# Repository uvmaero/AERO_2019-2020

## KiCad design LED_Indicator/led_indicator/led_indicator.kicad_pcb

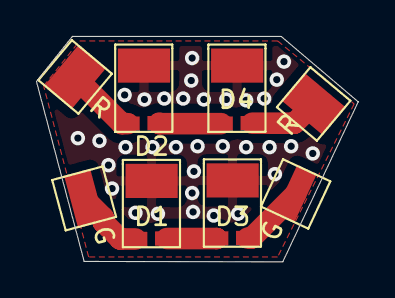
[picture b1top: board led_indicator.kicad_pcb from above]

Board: 2 copper layers, 17.9 x 12.5 mm, 8 parts (0 on the bottom side), 7 nets.

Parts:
D1, D2, D3, D4: LED_PAD; LXML-PM01
G: TestPoint; TestPoint_Pad_2.5x2.5mm
G#2: TestPoint; TestPoint_Pad_2.5x2.5mm
R: TestPoint; TestPoint_Pad_2.5x2.5mm
R#2: TestPoint; TestPoint_Pad_2.5x2.5mm

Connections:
/G_IN: D2.2, G#2.1
/G_OUT: D4.1, G.1
/R_IN: D1.2, R#2.1
/R_OUT: D3.1, R.1
/THM: D1.3, D2.3, D3.3, D4.3
unnamed: D1.1, D3.2
unnamed: D2.1, D4.2

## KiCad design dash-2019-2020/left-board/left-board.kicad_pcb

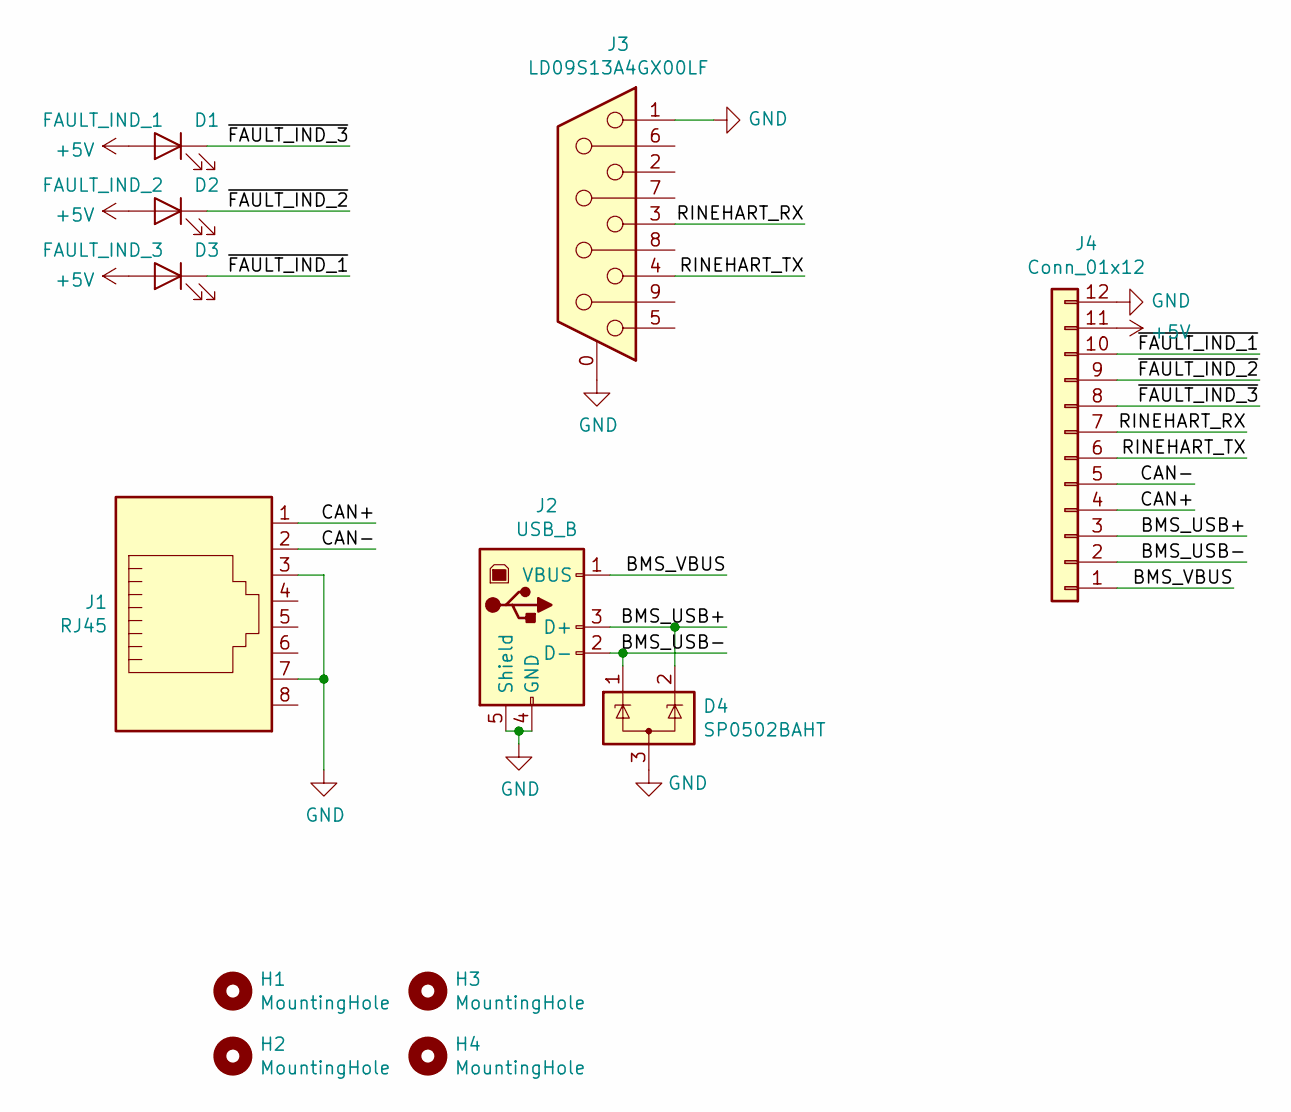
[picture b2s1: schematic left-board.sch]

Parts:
D1: FAULT_IND_1; LED_D5.0mm
D2: FAULT_IND_2; LED_D5.0mm
D3: FAULT_IND_3; LED_D5.0mm
D4: SP0502BAHT; SOT-23
H1, H2, H3, H4: MountingHole; MountingHole_3.2mm_M3
J1: RJ45; RJ45_Amphenol_54602-x08_Horizontal
J2: USB_B; USB_B_OST_USB-B1HSxx_Horizontal
J3: LD09S13A4GX00LF; DSUB-9_Female_Horizontal_P2.77x2.84mm_EdgePinOffset9.90mm_H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
J4: Conn_01x12; JST_PH_S12B-PH-K_1x12_P2.00mm_Horizontal

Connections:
+5V: D1.2 (A), D2.2 (A), D3.2 (A), J4.11
/BMS_USB+: D4.2 (K), J2.3 (D+), J4.3
/BMS_USB-: D4.1 (K), J2.2 (D-), J4.2
/BMS_VBUS: J2.1 (VBUS), J4.1
/CAN+: J1.1, J4.4
/CAN-: J1.2, J4.5
/RINEHART_RX: J3.3, J4.7
/RINEHART_TX: J3.4, J4.6
/~FAULT_IND_1: D3.1 (K), J4.10
/~FAULT_IND_2: D2.1 (K), J4.9
/~FAULT_IND_3: D1.1 (K), J4.8
GND: D4.3 (A), J1.3, J1.7, J2.4 (GND), J2.5 (Shield), J3.0 (PAD), J3.1, J4.12

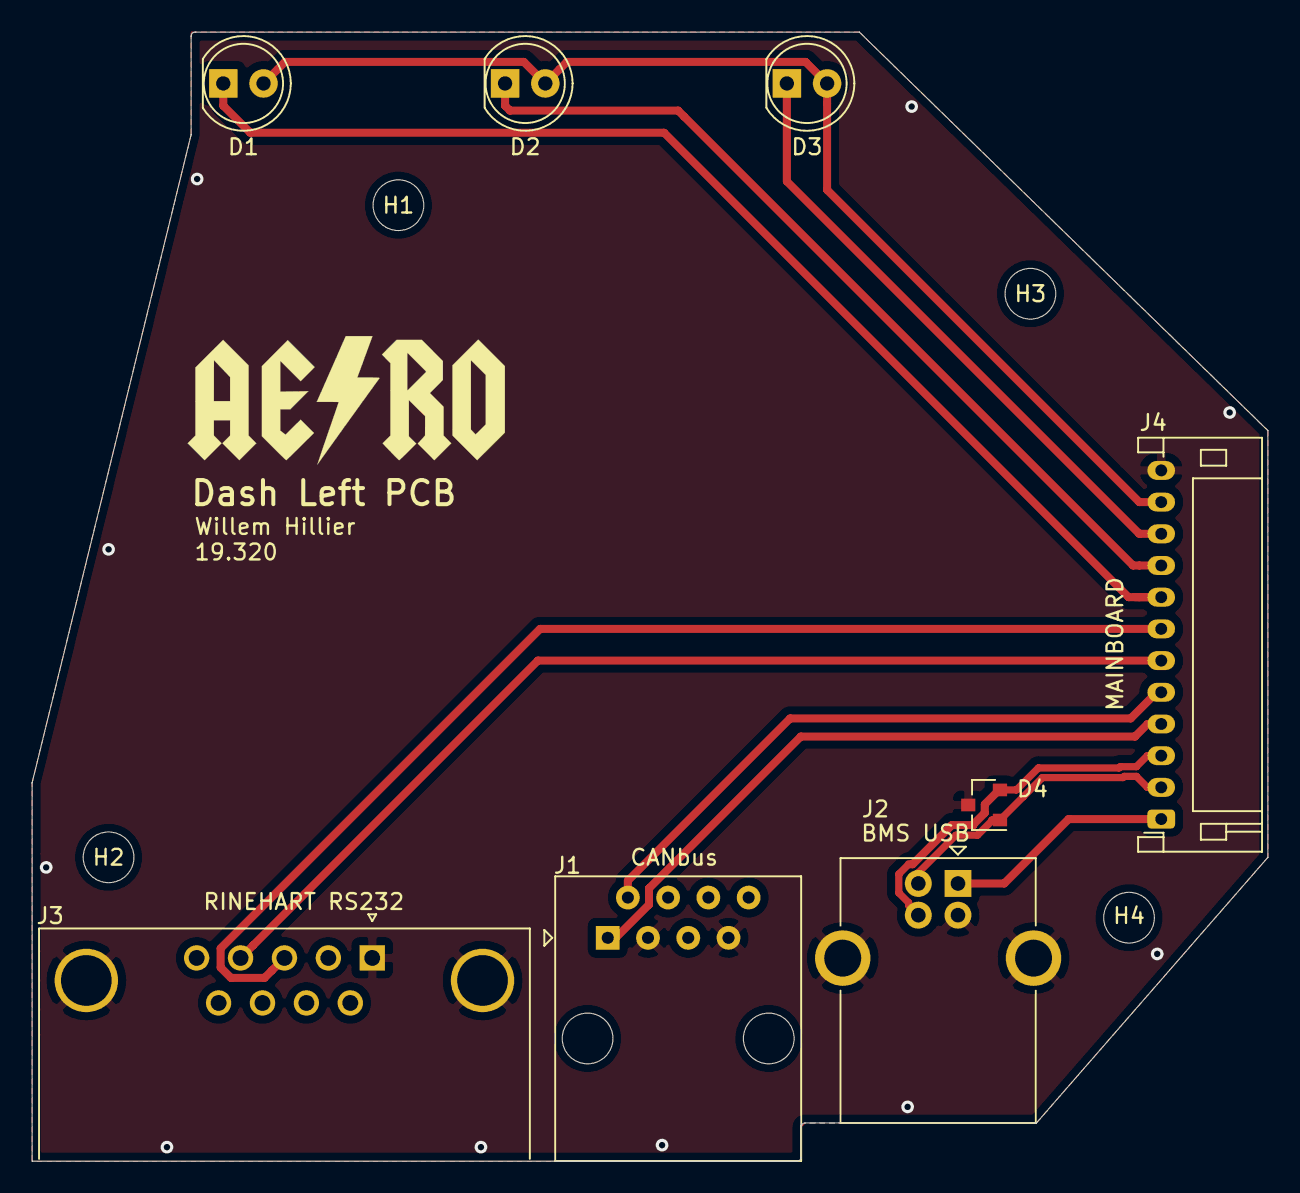
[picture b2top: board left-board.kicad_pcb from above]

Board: 2 copper layers, 78.0 x 71.2 mm, 12 parts (0 on the bottom side), 12 nets.

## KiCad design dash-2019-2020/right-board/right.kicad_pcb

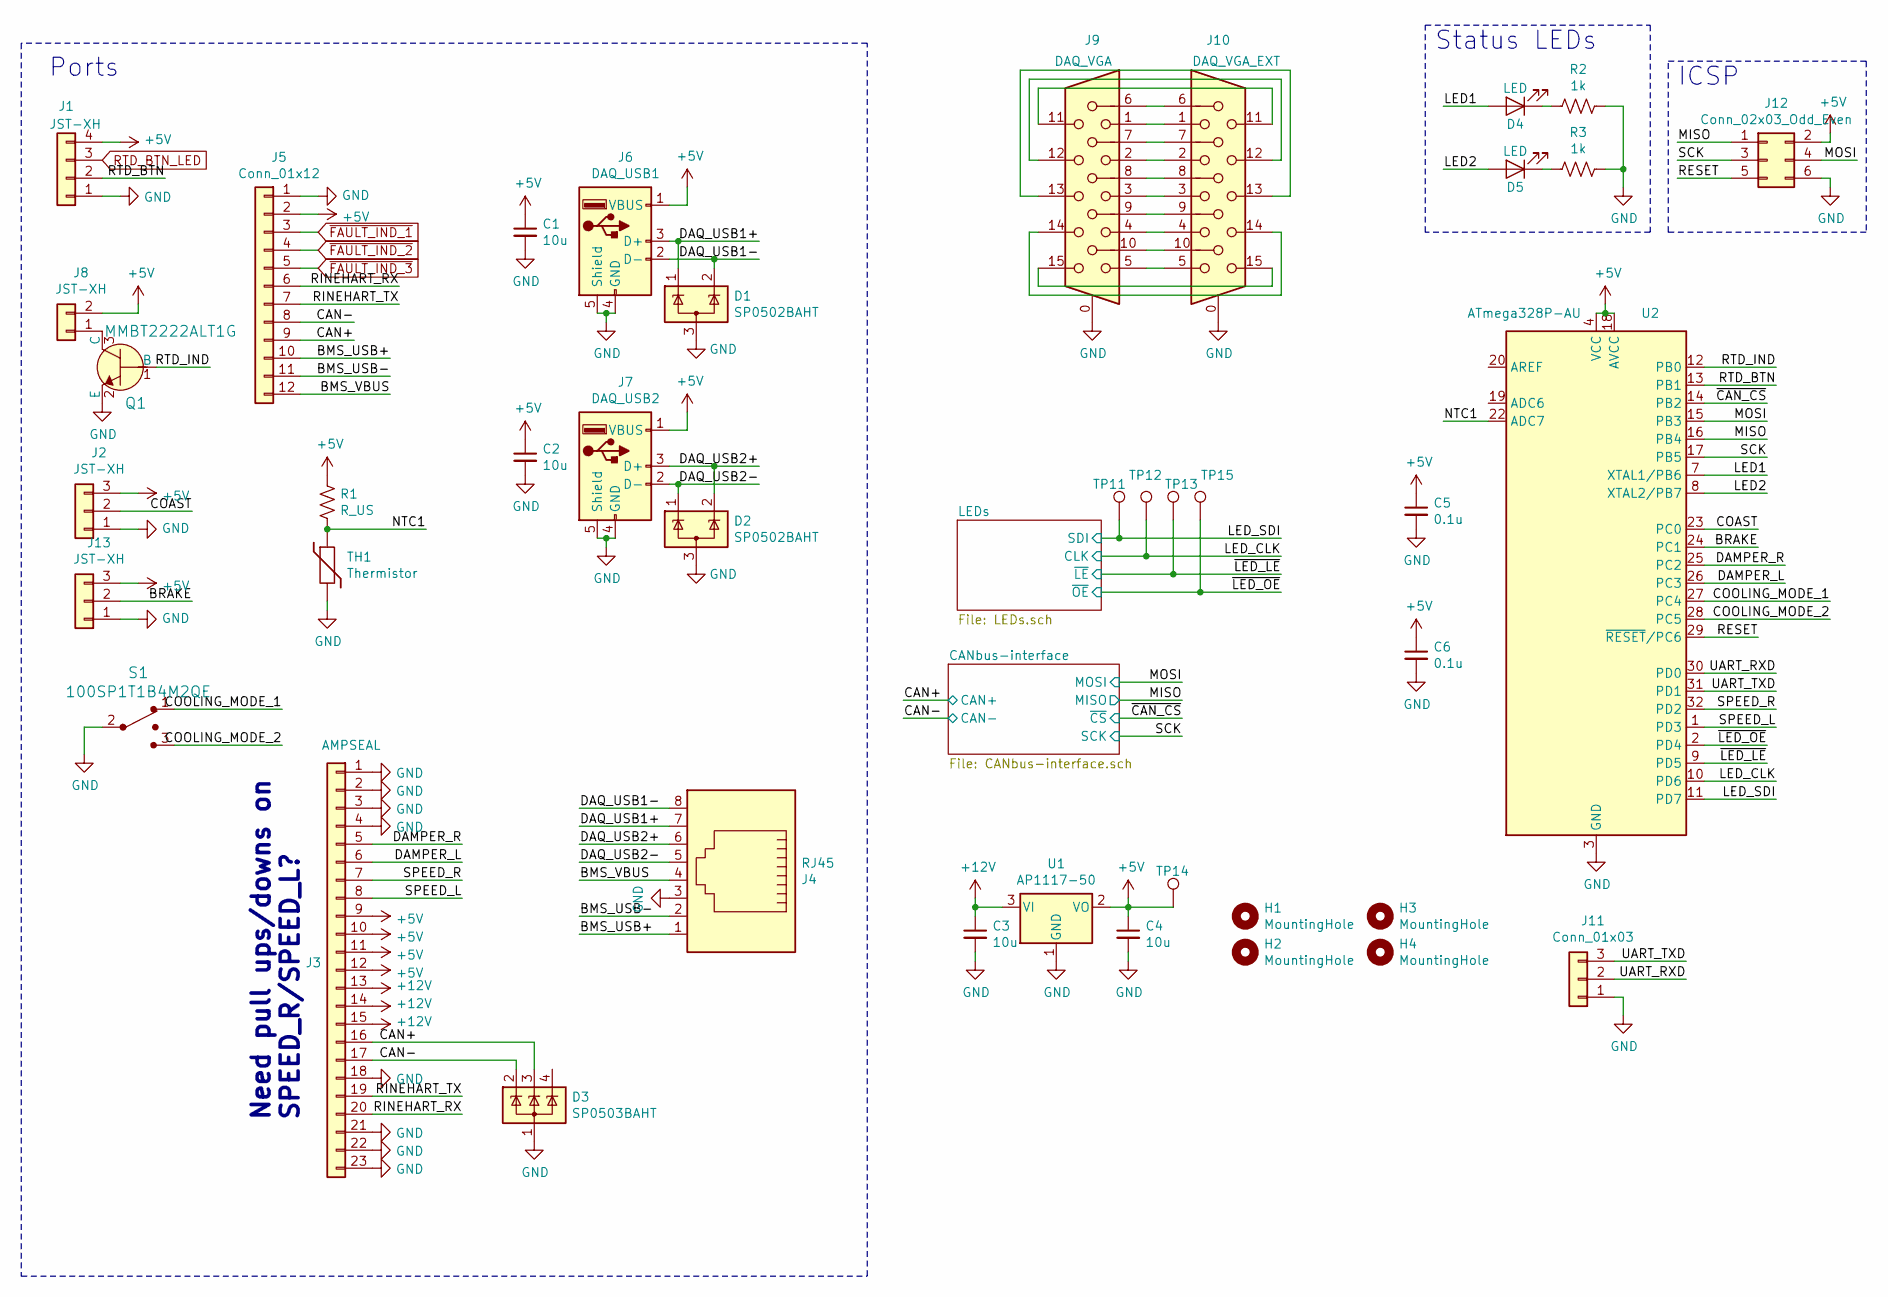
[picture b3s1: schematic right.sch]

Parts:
C1, C2, C4: 10u; C_0603_1608Metric
C3: 10u; C_0805_2012Metric
C5, C6: 0.1u; C_0603_1608Metric
D1, D2: SP0502BAHT; SOT-23
D3: SP0503BAHT; SOT-143
D4, D5: LED; LED_0603_1608Metric
H1, H2, H3, H4: MountingHole; MountingHole_3.2mm_M3
J1: JST-XH; JST_XH_S4B-XH-A_1x04_P2.50mm_Horizontal
J2, J13: JST-XH; JST_XH_S3B-XH-A_1x03_P2.50mm_Horizontal
J3: AMPSEAL; TE_1-776200-1_23pin_Vertical
J4: RJ45; RJ45_OST_PJ012-8P8CX_Vertical
J5: Conn_01x12; JST_PH_S12B-PH-K_1x12_P2.00mm_Horizontal
J6: DAQ_USB1; 87583-2010BLF
J7: DAQ_USB2; 87583-2010BLF
J8: JST-XH; JST_XH_S2B-XH-A_1x02_P2.50mm_Horizontal
J9: DAQ_VGA; DSUB-15-HD_Female_Vertical_P2.29x1.98mm_MountingHoles
J10: DAQ_VGA_EXT; DSUB-15-HD_Female_Horizontal_P2.29x2.54mm_EdgePinOffset8.35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
J11: Conn_01x03; PinHeader_1x03_P2.54mm_Vertical
J12: Conn_02x03_Odd_Even; PinHeader_2x03_P2.54mm_Vertical
Q1: MMBT2222ALT1G; SOT-23-3; MPN MMBT2222ALT1G; Digi-Key_PN MMBT2222ALT1GOSCT-ND
R1: R_US; R_0603_1608Metric
R2, R3: 1k; R_0603_1608Metric
S1: 100SP1T1B4M2QE; Toggle_Switch_100SP1T1B4M2QE; MPN 100SP1T1B4M2QE; Digi-Key_PN EG2355-ND
TH1: Thermistor; R_0603_1608Metric
TP11, TP12, TP13, TP14, TP15: TestPoint; TestPoint_Pad_D1.0mm
U1: AP1117-50; SOT-223-3_TabPin2
U2: ATmega328P-AU; TQFP-32_7x7mm_P0.8mm

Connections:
+5V: C1.1, C2.1, C4.1, C5.1, C6.1, J1.4, J2.3, J3.9, J3.10, J3.11, J3.12, J5.2, J6.1 (VBUS), J7.1 (VBUS), J8.2, J12.2, J13.3, R1.1, TP14.1, U1.2 (VO), U2.4 (VCC), U2.6 (VCC), U2.18 (AVCC); also elsewhere on the board
+12V: C3.1, J3.13, J3.14, J3.15, U1.3 (VI)
/BMS_USB+: J4.1, J5.10
/BMS_USB-: J4.2, J5.11
/BMS_VBUS: J4.4, J5.12
/BRAKE: J13.2, U2.24 (PC1)
/CAN+: D3.3 (K), J3.16, J5.9; also elsewhere on the board
/CAN-: D3.2 (K), J3.17, J5.8; also elsewhere on the board
/COAST: J2.2, U2.23 (PC0)
/COOLING_MODE_1: S1.1, U2.27 (PC4)
/COOLING_MODE_2: S1.3, U2.28 (PC5)
/DAMPER_L: J3.6, U2.26 (PC3)
/DAMPER_R: J3.5, U2.25 (PC2)
/DAQ_USB1+: D1.1 (K), J4.7, J6.3 (D+)
/DAQ_USB1-: D1.2 (K), J4.8, J6.2 (D-)
/DAQ_USB2+: D2.2 (K), J4.6, J7.3 (D+)
/DAQ_USB2-: D2.1 (K), J4.5, J7.2 (D-)
/LED1: D4.2 (A), U2.7 (XTAL1/PB6)
/LED2: D5.2 (A), U2.8 (XTAL2/PB7)
/LED_CLK: TP12.1, U2.10 (PD6); also elsewhere on the board
/LED_SDI: TP11.1, U2.11 (PD7); also elsewhere on the board
/MISO: J12.1, U2.16 (PB4); also elsewhere on the board
/MOSI: J12.4, U2.15 (PB3); also elsewhere on the board
/NTC1: R1.2, TH1.1, U2.22 (ADC7)
/RESET: J12.5, U2.29 (~RESET~/PC6)
/RINEHART_RX: J3.20, J5.6
/RINEHART_TX: J3.19, J5.7
/RTD_BTN: J1.2, U2.13 (PB1)
/RTD_IND: Q1.1 (B), U2.12 (PB0)
/SCK: J12.3, U2.17 (PB5); also elsewhere on the board
/SPEED_L: J3.8, U2.1 (PD3)
/SPEED_R: J3.7, U2.32 (PD2)
/UART_RXD: J11.2, U2.30 (PD0)
/UART_TXD: J11.3, U2.31 (PD1)
/~CAN_CS: U2.14 (PB2); also elsewhere on the board
/~LED_LE: TP13.1, U2.9 (PD5); also elsewhere on the board
/~LED_OE: TP15.1, U2.2 (PD4); also elsewhere on the board
GND: C1.2, C2.2, C3.2, C4.2, C5.2, C6.2, D1.3 (A), D2.3 (A), D3.1 (A), J1.1, J2.1, J3.1, J3.2, J3.3, J3.4, J3.18, J3.21, J3.22, J3.23, J4.3, J5.1, J6.4 (GND), J6.5 (Shield), J7.4 (GND), J7.5 (Shield), J9.0, J10.0, J11.1, J12.6, J13.1, Q1.2 (E), R2.1, R3.1, S1.2 (Com), TH1.2, U1.1 (GND), U2.3 (GND), U2.5 (GND), U2.21 (GND); also elsewhere on the board
unnamed: D4.1 (K), R2.2
unnamed: D5.1 (K), R3.2
unnamed: J8.1, Q1.3 (C)
unnamed: J9.1, J10.1
unnamed: J9.2, J10.2
unnamed: J9.3, J10.3
unnamed: J9.4, J10.4
unnamed: J9.5, J10.5
unnamed: J9.6, J10.6
unnamed: J9.7, J10.7
unnamed: J9.8, J10.8
unnamed: J9.9, J10.9
unnamed: J9.10, J10.10
unnamed: J9.11, J10.11
unnamed: J9.12, J10.12
unnamed: J9.13, J10.13
unnamed: J9.14, J10.14
unnamed: J9.15, J10.15
RTD_BTN_LED: J1.3; also elsewhere on the board
~FAULT_IND_1: J5.3; also elsewhere on the board
~FAULT_IND_2: J5.4; also elsewhere on the board
~FAULT_IND_3: J5.5; also elsewhere on the board

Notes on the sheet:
ICSP
Status LEDs
Ports
Need pull ups/downs on SPEED_R/SPEED_L?

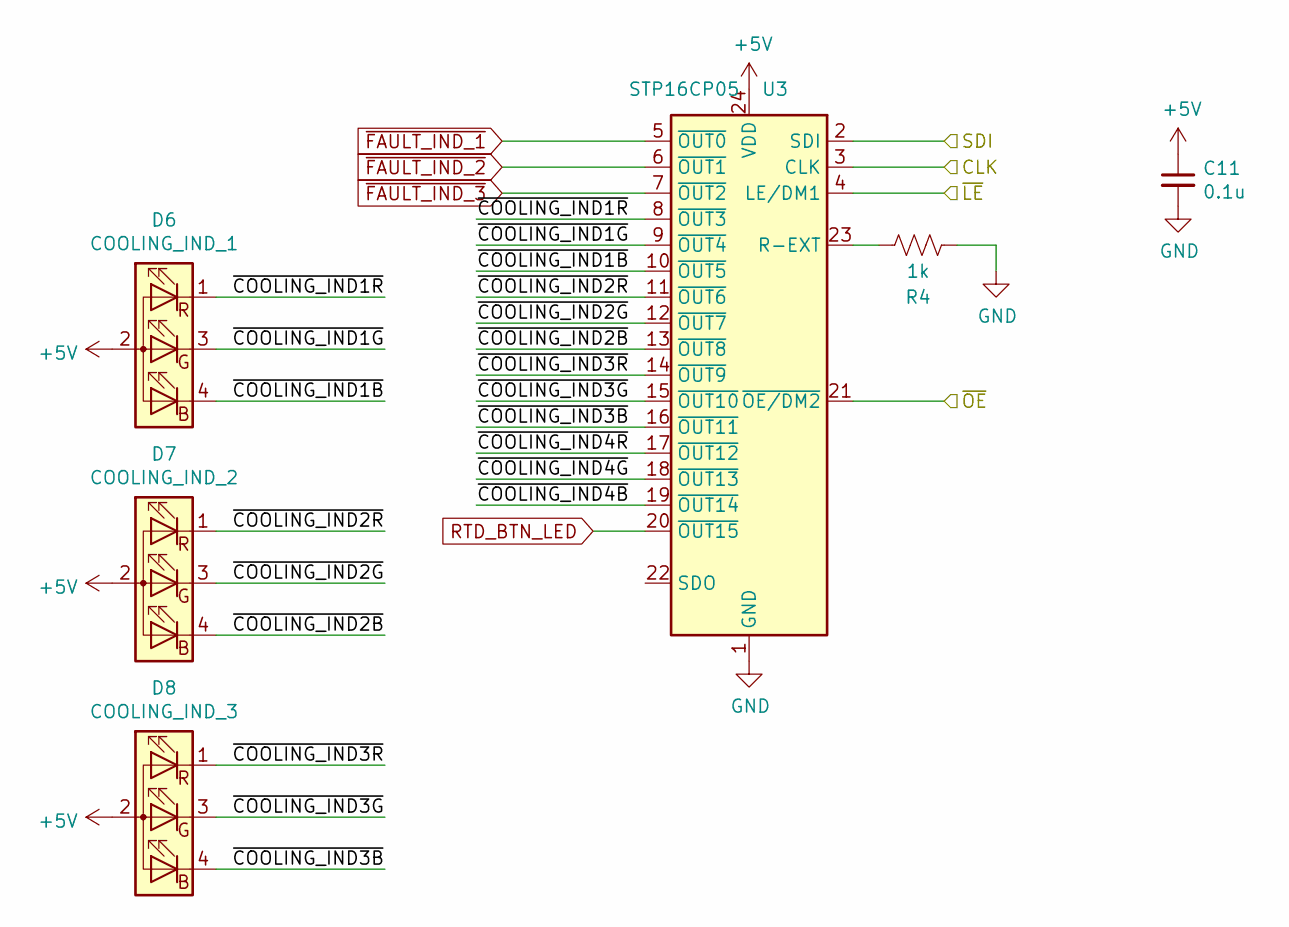
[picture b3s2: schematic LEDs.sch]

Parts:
C11: 0.1u; C_0603_1608Metric
D6: COOLING_IND_1; LED_D5.0mm-4_RGB
D7: COOLING_IND_2; LED_D5.0mm-4_RGB
D8: COOLING_IND_3; LED_D5.0mm-4_RGB
R4: 1k; R_0603_1608Metric
U3: STP16CP05; TSSOP-24_4.4x7.8mm_P0.65mm

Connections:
+5V: C11.1, D6.2 (A), D7.2 (A), D8.2 (A), U3.24 (VDD); also elsewhere on the board
/LED_CLK: U3.3 (CLK); also elsewhere on the board
/LED_SDI: U3.2 (SDI); also elsewhere on the board
/LEDs/~COOLING_IND1B: D6.4 (BK), U3.10 (~OUT5)
/LEDs/~COOLING_IND1G: D6.3 (GK), U3.9 (~OUT4)
/LEDs/~COOLING_IND1R: D6.1 (RK), U3.8 (~OUT3)
/LEDs/~COOLING_IND2B: D7.4 (BK), U3.13 (~OUT8)
/LEDs/~COOLING_IND2G: D7.3 (GK), U3.12 (~OUT7)
/LEDs/~COOLING_IND2R: D7.1 (RK), U3.11 (~OUT6)
/LEDs/~COOLING_IND3B: D8.4 (BK), U3.16 (~OUT11)
/LEDs/~COOLING_IND3G: D8.3 (GK), U3.15 (~OUT10)
/LEDs/~COOLING_IND3R: D8.1 (RK), U3.14 (~OUT9)
/LEDs/~COOLING_IND4B: U3.19 (~OUT14)
/LEDs/~COOLING_IND4G: U3.18 (~OUT13)
/LEDs/~COOLING_IND4R: U3.17 (~OUT12)
/~LED_LE: U3.4 (LE/DM1); also elsewhere on the board
/~LED_OE: U3.21 (~OE/DM2); also elsewhere on the board
GND: C11.2, R4.1, U3.1 (GND); also elsewhere on the board
unnamed: R4.2, U3.23 (R-EXT)
RTD_BTN_LED: U3.20 (~OUT15); also elsewhere on the board
~FAULT_IND_1: U3.5 (~OUT0); also elsewhere on the board
~FAULT_IND_2: U3.6 (~OUT1); also elsewhere on the board
~FAULT_IND_3: U3.7 (~OUT2); also elsewhere on the board

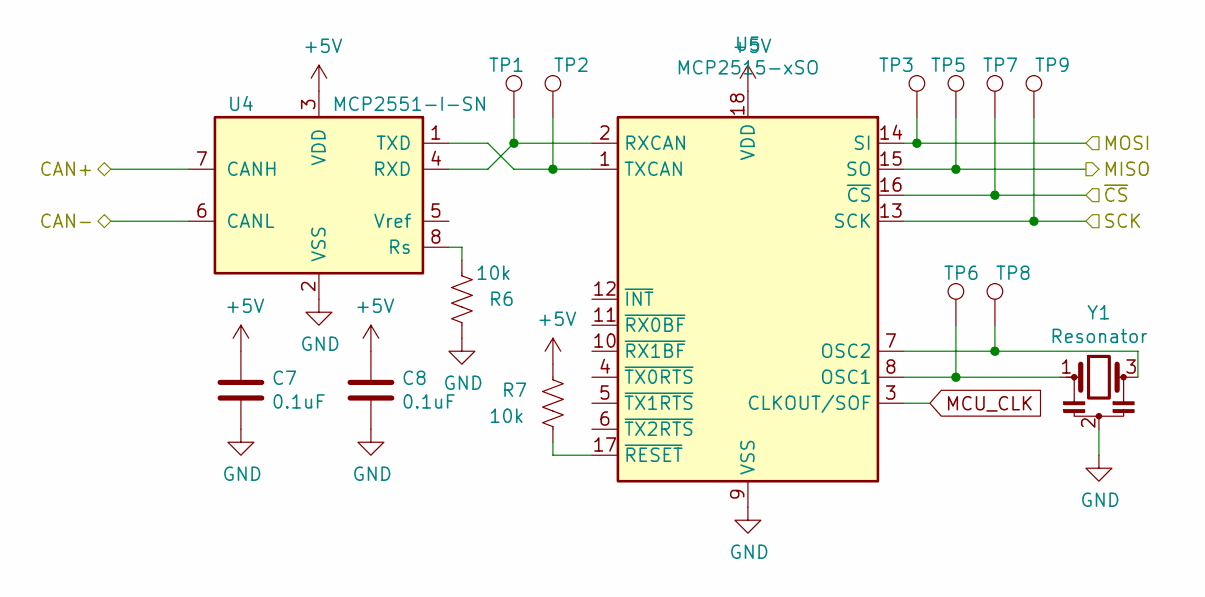
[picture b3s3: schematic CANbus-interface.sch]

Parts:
C7, C8: 0.1uF; C_0603_1608Metric
R6, R7: 10k; R_0603_1608Metric
TP1, TP2, TP3, TP5, TP6, TP7, TP8, TP9: TestPoint; TestPoint_Pad_D1.0mm
U4: MCP2551-I-SN; SOIC-8_3.9x4.9mm_P1.27mm
U5: MCP2515-xSO; SOIC-18W_7.5x11.6mm_P1.27mm
Y1: Resonator; Resonator_SMD_muRata_CSTxExxV-3Pin_3.0x1.1mm

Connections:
+5V: C7.1, C8.1, R7.1, U4.3 (VDD), U5.18 (VDD); also elsewhere on the board
/CAN+: U4.7 (CANH); also elsewhere on the board
/CAN-: U4.6 (CANL); also elsewhere on the board
/MISO: TP5.1, U5.15 (SO); also elsewhere on the board
/MOSI: TP3.1, U5.14 (SI); also elsewhere on the board
/SCK: TP9.1, U5.13 (SCK); also elsewhere on the board
/~CAN_CS: TP7.1, U5.16 (~CS); also elsewhere on the board
GND: C7.2, C8.2, R6.2, U4.2 (VSS), U5.9 (VSS), Y1.2; also elsewhere on the board
MCU_CLK: U5.3 (CLKOUT/SOF)
unnamed: R6.1, U4.8 (Rs)
unnamed: R7.2, U5.17 (~RESET)
unnamed: TP1.1, U4.4 (RXD), U5.2 (RXCAN)
unnamed: TP2.1, U4.1 (TXD), U5.1 (TXCAN)
unnamed: TP6.1, U5.8 (OSC1), Y1.1
unnamed: TP8.1, U5.7 (OSC2), Y1.3

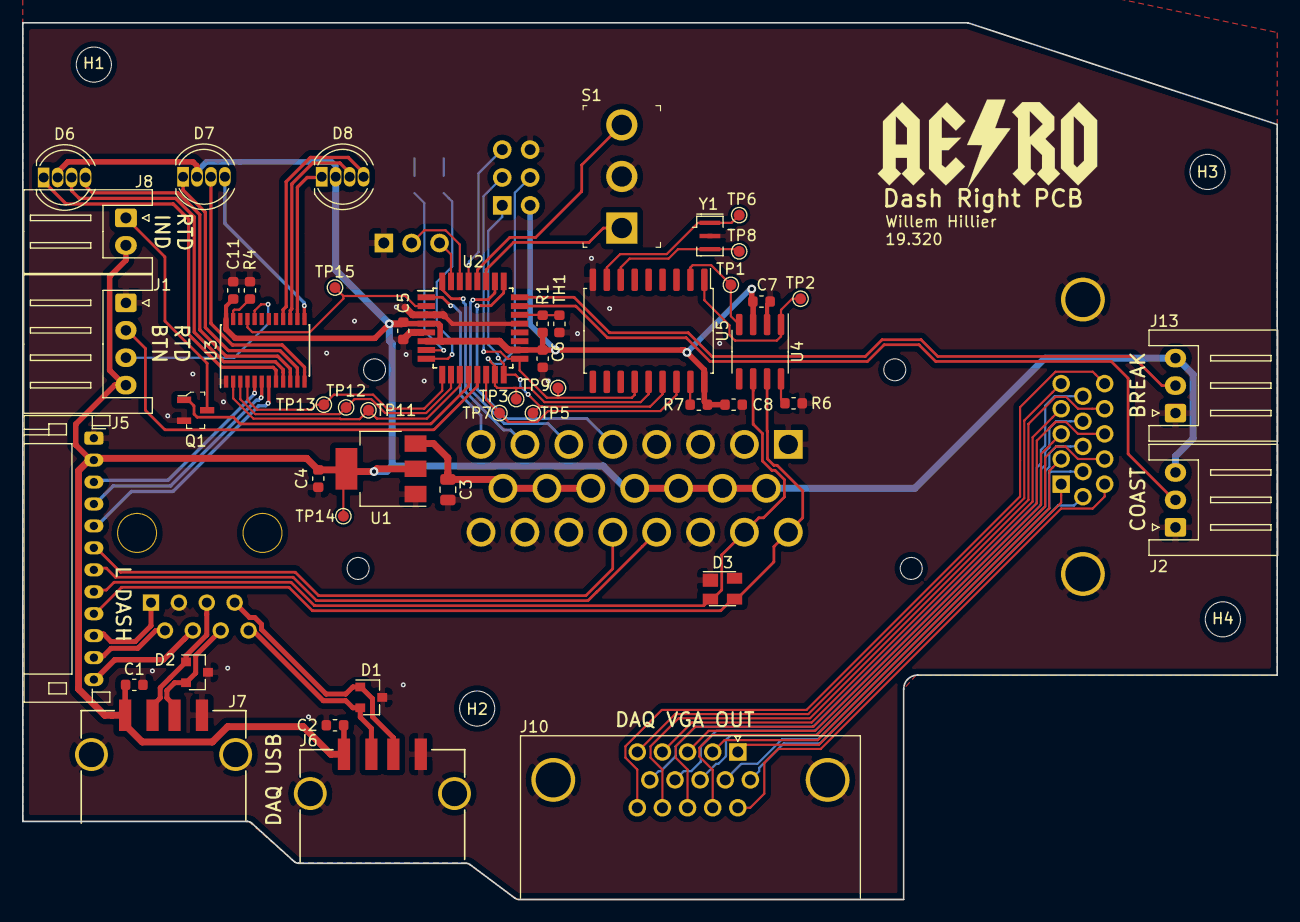
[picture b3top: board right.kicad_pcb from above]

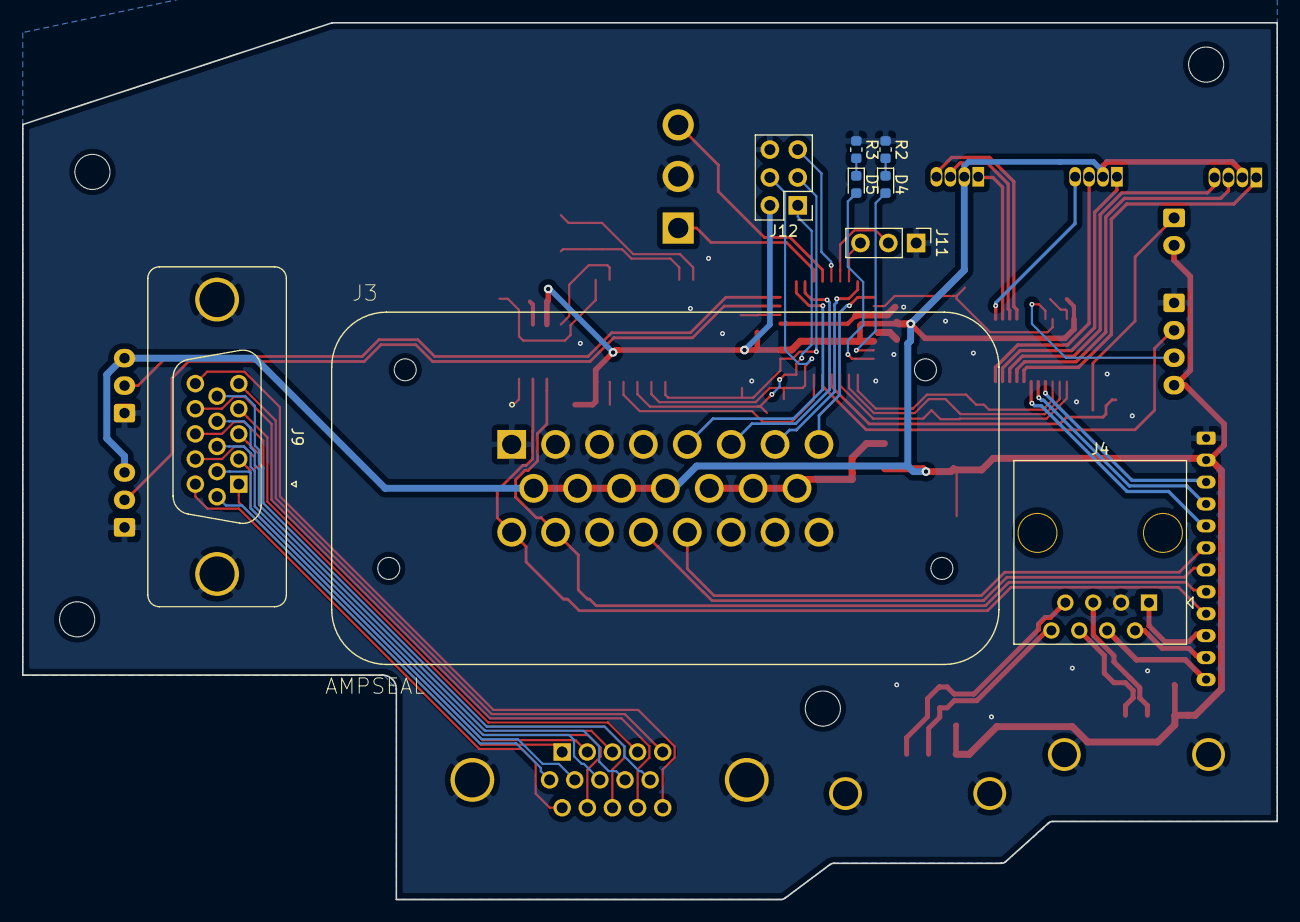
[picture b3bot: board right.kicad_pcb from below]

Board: 2 copper layers, 114.3 x 79.9 mm, 62 parts (9 on the bottom side), 76 nets.

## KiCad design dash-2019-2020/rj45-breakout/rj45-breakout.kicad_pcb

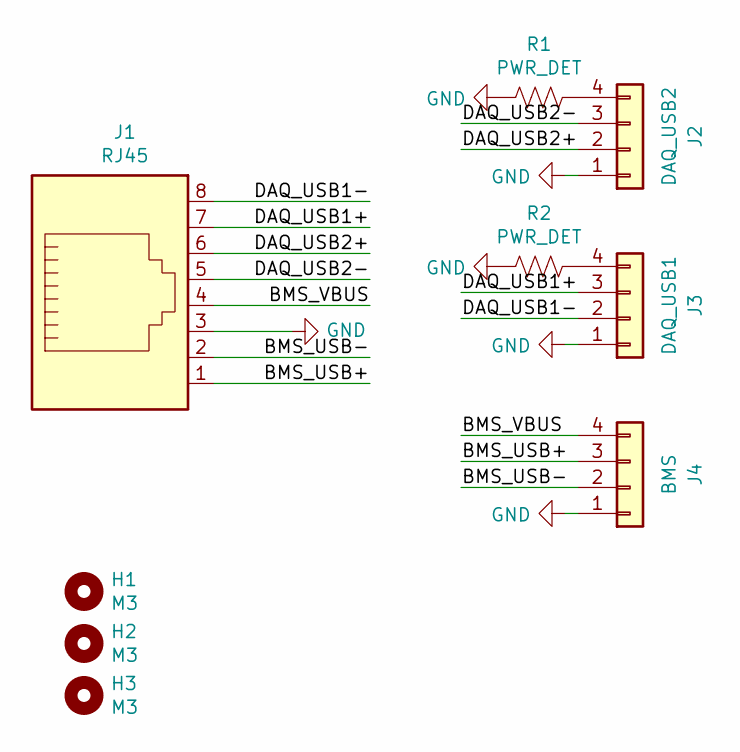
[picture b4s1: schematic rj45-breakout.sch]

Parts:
H1, H2, H3: M3; MountingHole_3.2mm_M3
J1: RJ45; RJ45_Amphenol_54602-x08_Horizontal
J2: DAQ_USB2; JST_PH_S4B-PH-K_1x04_P2.00mm_Horizontal
J3: DAQ_USB1; JST_PH_S4B-PH-K_1x04_P2.00mm_Horizontal
J4: BMS; JST_PH_S4B-PH-K_1x04_P2.00mm_Horizontal
R1, R2: PWR_DET; R_0603_1608Metric

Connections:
/BMS_USB+: J1.1, J4.3
/BMS_USB-: J1.2, J4.2
/BMS_VBUS: J1.4, J4.4
/DAQ_USB1+: J1.7, J3.3
/DAQ_USB1-: J1.8, J3.2
/DAQ_USB2+: J1.6, J2.2
/DAQ_USB2-: J1.5, J2.3
GND: J1.3, J2.1, J3.1, J4.1, R1.2, R2.2
unnamed: J2.4, R1.1
unnamed: J3.4, R2.1

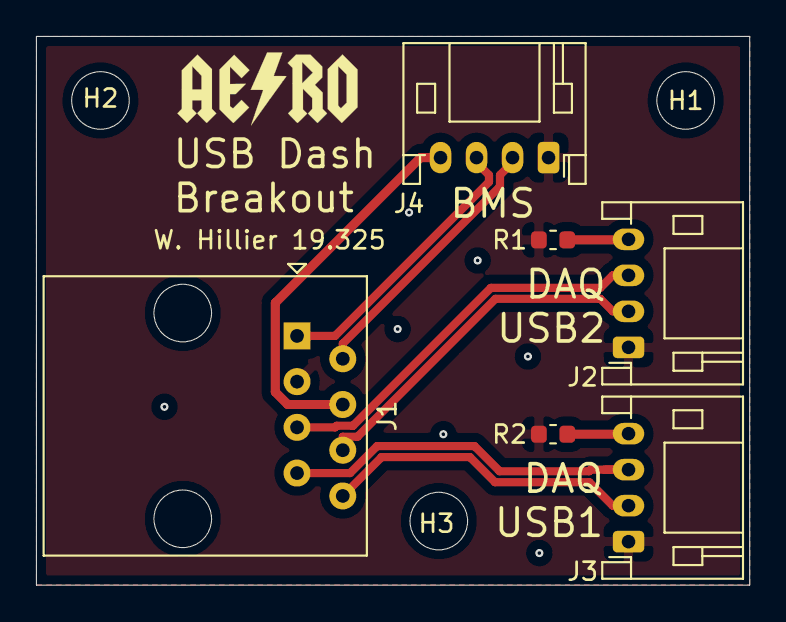
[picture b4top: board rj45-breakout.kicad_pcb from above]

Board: 2 copper layers, 39.6 x 30.5 mm, 9 parts (0 on the bottom side), 10 nets.

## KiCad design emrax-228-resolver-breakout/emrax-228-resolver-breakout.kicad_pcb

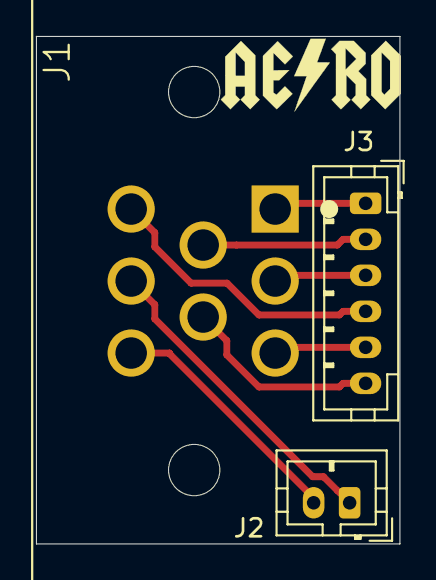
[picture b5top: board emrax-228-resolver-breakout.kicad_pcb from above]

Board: 2 copper layers, 20.2 x 28.2 mm, 3 parts (0 on the bottom side), 8 nets.

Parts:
J1: AMPSEAL; TE_1-776280-1_8pin_Horizontal
J2: THERMISTOR; JST_PH_B2B-PH-K_1x02_P2.00mm_Vertical
J3: RESOLVER; JST_PH_B6B-PH-K_1x06_P2.00mm_Vertical

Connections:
/COS+: J1.3, J3.5
/COS-: J1.6, J3.4
/EXC+: J1.5, J3.6
/SIN+: J1.2, J3.3
/SIN-: J1.4, J3.2
/TEMP+: J1.7, J2.1
/TEMP-: J1.8, J2.2
GND: J1.1, J3.1
